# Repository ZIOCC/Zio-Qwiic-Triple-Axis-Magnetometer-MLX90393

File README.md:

# Zio Qwiic Triple Axis Magnetometer (MLX90393)

> This product can be available for purchase [here](https://www.smart-prototyping.com/Zio-QwiIc-Triple-Axis-Magnetometer-MLX90393).

#### Description

This ZIO Qwiic board can be used as one of the Four Great Inventions: the compass. The board is a triple-axis magnetometer compass used to detect magnetic forces, mostly used to detect magnetic North. 
But magnetometers have many other uses such as detecting magnetic materials. 
 
The board features a MLX90393 sensor that incorporates both I2C and, able to sense a wide range of fields from small ones such as Earth’s magnetic field to larger magnetic fields. But the compass is not the only application for it, it can also be used for non-contact HMI applications (such as rotary knobs and joysticks), home security, liquid level sensing, position sensing and magnetic fingerprint detection. 
 
The resolution rate for the sensor is 0.161µ with an operating voltage range of 2.2V to 3.6V at 100µA. 
In addition, the I2C address can be changed thanks to the jumper pads on the back of the board (A0/ A1)  and the mode can also be changed to SPI thought the jumper pads. 

#### Specification

* Operation Voltage: 2.2V to 3.3V
* Relative Humidity: ±2%
* Temperature: ±0.3 °C
* IC: MLX90393
* I2C address: 0x0C, 0x0D, 0x0E, 0x0F (Default: 0x0C)
* Dimensions: 25.5 x 26.8mm
* Weight: 1.6g

#### Links

* [PCB source file (eagle file, schematic, Gerber files)](https://github.com/ZIOCC/Zio-Qwiic-Triple-Axis-Magnetometer-MLX90393)
* [MLX90393 Datasheet](https://cdn.sparkfun.com/assets/e/e/f/2/7/MLX90393-Datasheet-Melexis.PDF)
* [Library Code](https://github.com/tedyapo/arduino-MLX90393)

> ###### About Zio
> Zio is a new line of open sourced, compact, and grid layout boards, fully integrated for Arduino and Qwiic ecosystem. Designed ideally for wearables, robotics, small-space limitations or other on the go projects. Check out other awesome Zio products [here](https://www.smart-prototyping.com/Zio).

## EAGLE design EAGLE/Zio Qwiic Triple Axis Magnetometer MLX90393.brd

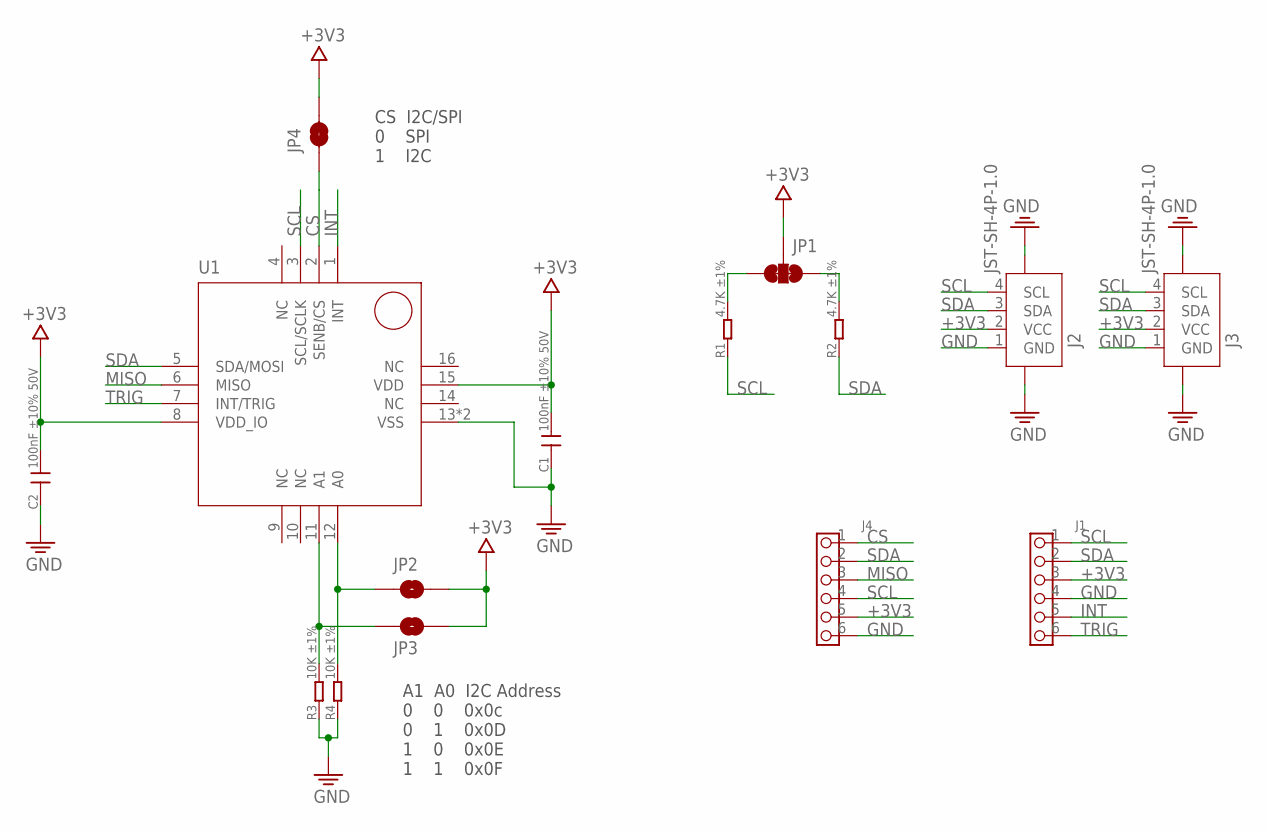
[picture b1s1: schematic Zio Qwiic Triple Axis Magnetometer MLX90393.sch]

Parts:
C1, C2: 100nF ±10% 50V; C0603
J1, J4: HEADER-6P-60/35MIL; 6P-2.54-60/35MIL
J2, J3: JST-SH-4P-1.0; JST-SH-4P
JP1: SMT-JUMPER_3_2-NC_TRACE
JP2, JP3: JUMPER-SMT_2_NC_PASTE_NOCREM; SMT-JUMPER_2_NC_PASTE_SILK_NOCREM
JP4: JUMPER-SMT_2_NC_TRACE; SMT-JUMPER_2_NC_TRACE
R1, R2: 4.7K ±1%; R0603
R3, R4: 10K ±1%; R0603
U1: MLX90393; QFN16-3*3

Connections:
+3V3: C1.2, C2.2, J1.3, J2.2 (VCC), J3.2 (VCC), J4.5, JP1.2, JP2.2, JP3.2, JP4.2, U1.8 (VDD_IO), U1.15 (VDD)
CS: J4.1, JP4.1, U1.2 (SENB/CS)
GND: C1.1, C2.1, J1.4, J2.1 (GND), J2.NC1 (5), J2.NC2 (6), J3.1 (GND), J3.NC1 (5), J3.NC2 (6), J4.6, R3.1, R4.1, U1.13 (VSS), U1.PAD (VSS)
INT: J1.5, U1.1 (INT)
MISO: J4.3, U1.6 (MISO)
unnamed: JP3.1, R3.2, U1.11 (A1)
unnamed: JP2.1, R4.2, U1.12 (A0)
unnamed: JP1.3, R1.2
unnamed: JP1.1, R2.2
SCL: J1.1, J2.4 (SCL), J3.4 (SCL), J4.4, R1.1, U1.3 (SCL/SCLK)
SDA: J1.2, J2.3 (SDA), J3.3 (SDA), J4.2, R2.1, U1.5 (SDA/MOSI)
TRIG: J1.6, U1.7 (INT/TRIG)

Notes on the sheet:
A1 A0 I2C Address 0 0 0x0c 0 1 0x0D 1 0 0x0E 1 1 0x0F
CS I2C/SPI 0 SPI 1 I2C

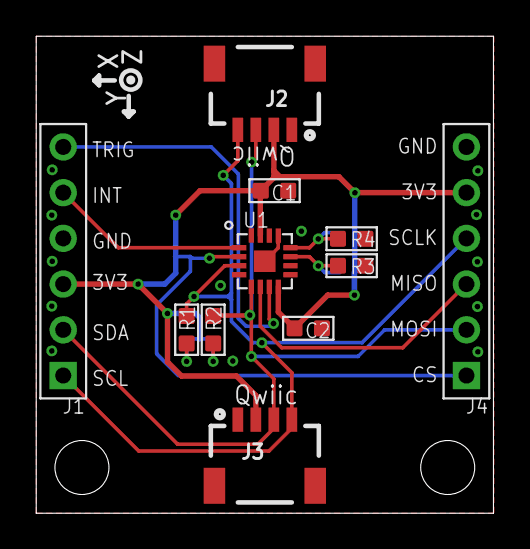
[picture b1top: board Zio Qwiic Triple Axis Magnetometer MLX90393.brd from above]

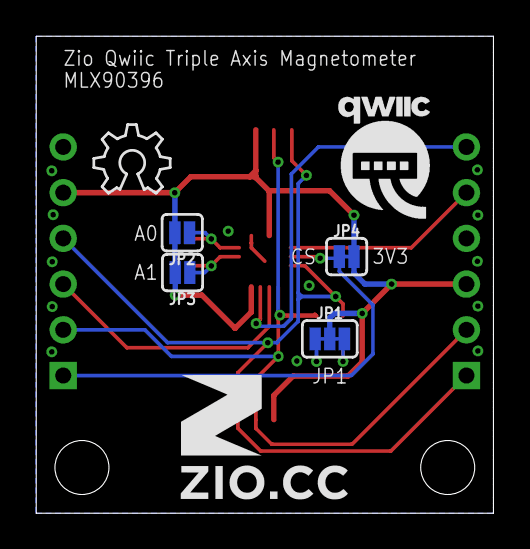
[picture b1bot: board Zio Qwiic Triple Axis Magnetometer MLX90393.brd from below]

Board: 2 copper layers, 25.4 x 26.5 mm, 18 parts (7 on the bottom side), 12 nets.

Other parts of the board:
U$6: 7MM
U$7: QWIIC-LOGO-MEDIUM
U$8: OSHW_6X150_NOTEXT
